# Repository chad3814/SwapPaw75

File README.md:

# SwapPaw75

The SwapPaw75 is a clone of the [Southpaw75](https://github.com/kelvinhall05/Southpaw75) budget FR4 keyboard with support for hotswap sockets.

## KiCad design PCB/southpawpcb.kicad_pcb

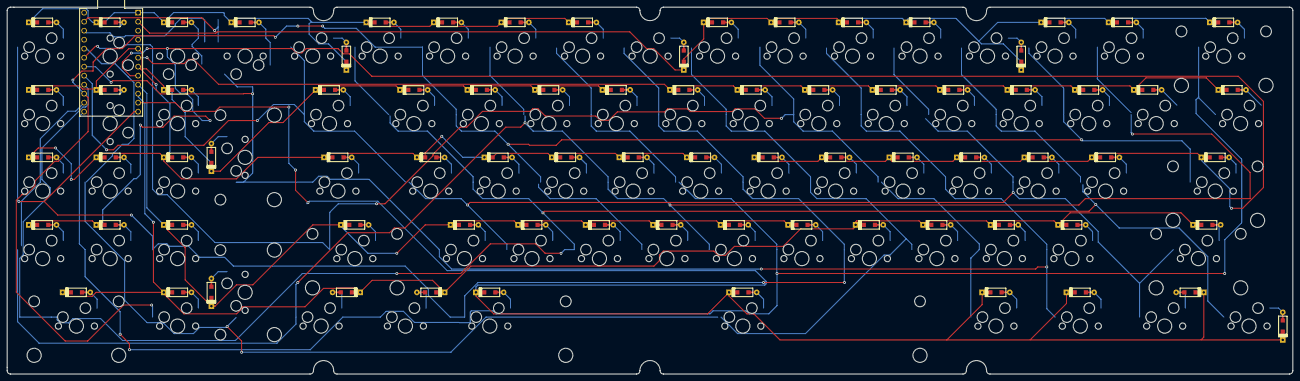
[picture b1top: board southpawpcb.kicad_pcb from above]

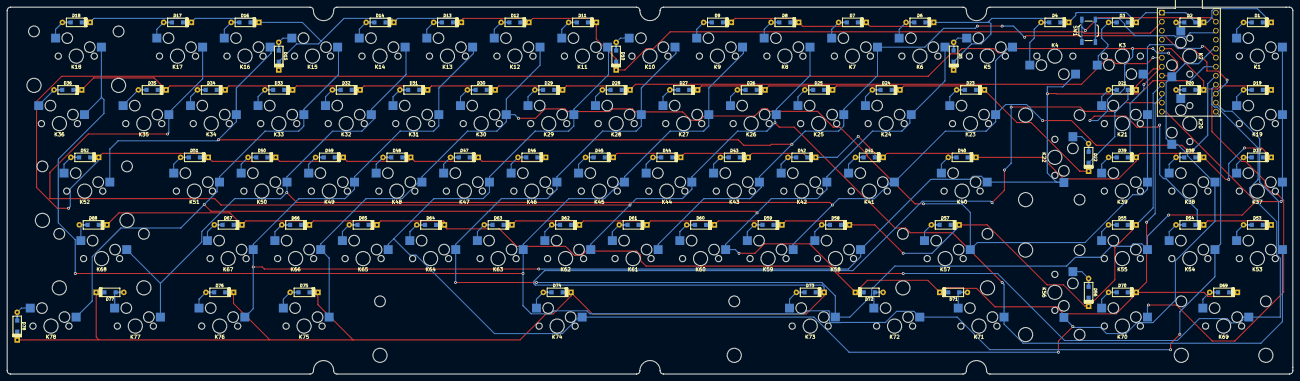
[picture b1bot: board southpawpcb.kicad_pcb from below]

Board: 2 copper layers, 362.9 x 103.6 mm, 158 parts (80 on the bottom side), 98 nets.

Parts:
D1, D2, D3, D4, D5, D6, D7, D8, D9, D10, D11, D12, D13, D14, D15, D16, D17, D18, D19, D20, D21, D22, D23, D24, D25, D26, D27, D28, D29, D30, D31, D32, D33, D34, D35, D36, D37, D38, D39, D40, D41, D42, D43, D44, D45, D46, D47, D48, D49, D50, D51, D52, D53, D54, D55, D56, D57, D58, D59, D60, D61, D62, D63, D64, D65, D66, D67, D68, D69, D70, D71, D72, D73, D74, D75, D76, D77, D78: D; D_SOD123_axial-dual
K1, K2, K3, K4, K5, K6, K7, K8, K9, K10, K11, K12, K13, K14, K15, K16, K17, K19, K20, K21, K24, K25, K26, K27, K28, K29, K30, K31, K32, K33, K34, K35, K37, K38, K39, K41, K42, K43, K44, K45, K46, K47, K48, K49, K50, K51, K53, K54, K55, K58, K59, K60, K61, K62, K63, K64, K65, K66, K67, K70: KEYSW; MXOnly-1U-Hotswap
K18, K22, K56, K69: KEYSW; MXOnly-2U-Hotswap
K23, K36: KEYSW; MXOnly-1.5U-Hotswap
K40: KEYSW; MXOnly-1.75U-Hotswap
K52, K57: KEYSW; MXOnly-2.25U-Hotswap
K68: KEYSW; MXOnly-2.75U-Hotswap
K71, K72, K73, K75, K76, K77, K78: KEYSW; MXOnly-1.25U-Hotswap
K74: KEYSW; MXOnly-6.25U-Hotswap
SW1: Reset; SW_SPST_TL3342
U1: ProMicro

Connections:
unnamed: D1.1 (K), D2.1 (K), D3.1 (K), D4.1 (K), D5.1 (K), D6.1 (K), D7.1 (K), D8.1 (K), D9.1 (K), U1.1 (TX)
unnamed: D1.2 (A), K1.2 (ROW)
unnamed: D2.2 (A), K2.1 (COL)
unnamed: D3.2 (A), K3.1 (COL)
unnamed: D4.2 (A), K4.1 (COL)
unnamed: D5.2 (A), K5.2 (ROW)
unnamed: D6.2 (A), K6.2 (ROW)
unnamed: D7.2 (A), K7.2 (ROW)
unnamed: D8.2 (A), K8.2 (ROW)
unnamed: D9.2 (A), K9.2 (ROW)
unnamed: D10.1 (K), D11.1 (K), D12.1 (K), D13.1 (K), D14.1 (K), D15.1 (K), D16.1 (K), D17.1 (K), D18.1 (K), U1.2 (RX)
unnamed: D10.2 (A), K10.2 (ROW)
unnamed: D11.2 (A), K11.2 (ROW)
unnamed: D12.2 (A), K12.2 (ROW)
unnamed: D13.2 (A), K13.2 (ROW)
unnamed: D14.2 (A), K14.2 (ROW)
unnamed: D15.2 (A), K15.2 (ROW)
unnamed: D16.2 (A), K16.2 (ROW)
unnamed: D17.2 (A), K17.2 (ROW)
unnamed: D18.2 (A), K18.2 (ROW)
unnamed: D19.1 (K), D20.1 (K), D21.1 (K), D22.1 (K), D23.1 (K), D24.1 (K), D25.1 (K), D26.1 (K), D27.1 (K), U1.5 (SCL)
unnamed: D19.2 (A), K19.2 (ROW)
unnamed: D20.2 (A), K20.1 (COL)
unnamed: D21.2 (A), K21.2 (ROW)
unnamed: D22.2 (A), K22.2 (ROW)
unnamed: D23.2 (A), K23.2 (ROW)
unnamed: D24.2 (A), K24.2 (ROW)
unnamed: D25.2 (A), K25.2 (ROW)
unnamed: D26.2 (A), K26.2 (ROW)
unnamed: D27.2 (A), K27.2 (ROW)
unnamed: D28.1 (K), D29.1 (K), D30.1 (K), D31.1 (K), D32.1 (K), D33.1 (K), D34.1 (K), D35.1 (K), D36.1 (K), U1.6 (SDA)
unnamed: D28.2 (A), K28.2 (ROW)
unnamed: D29.2 (A), K29.2 (ROW)
unnamed: D30.2 (A), K30.2 (ROW)
unnamed: D31.2 (A), K31.2 (ROW)
unnamed: D32.2 (A), K32.2 (ROW)
unnamed: D33.2 (A), K33.2 (ROW)
unnamed: D34.2 (A), K34.2 (ROW)
unnamed: D35.2 (A), K35.2 (ROW)
unnamed: D36.2 (A), K36.2 (ROW)
unnamed: D37.1 (K), D38.1 (K), D39.1 (K), D40.1 (K), D41.1 (K), D42.1 (K), D43.1 (K), D44.1 (K), D45.1 (K), U1.7 (D4)
unnamed: D37.2 (A), K37.2 (ROW)
unnamed: D38.2 (A), K38.2 (ROW)
unnamed: D39.2 (A), K39.2 (ROW)
unnamed: D40.2 (A), K40.2 (ROW)
unnamed: D41.2 (A), K41.2 (ROW)
unnamed: D42.2 (A), K42.2 (ROW)
unnamed: D43.2 (A), K43.2 (ROW)
unnamed: D44.2 (A), K44.2 (ROW)
unnamed: D45.2 (A), K45.2 (ROW)
unnamed: D46.1 (K), D47.1 (K), D48.1 (K), D49.1 (K), D50.1 (K), D51.1 (K), D52.1 (K), D53.1 (K), D54.1 (K), U1.8 (C6)
unnamed: D46.2 (A), K46.2 (ROW)
unnamed: D47.2 (A), K47.2 (ROW)
unnamed: D48.2 (A), K48.2 (ROW)
unnamed: D49.2 (A), K49.2 (ROW)
unnamed: D50.2 (A), K50.2 (ROW)
unnamed: D51.2 (A), K51.2 (ROW)
unnamed: D52.2 (A), K52.2 (ROW)
unnamed: D53.2 (A), K53.2 (ROW)
unnamed: D54.2 (A), K54.2 (ROW)
unnamed: D55.1 (K), D56.1 (K), D57.1 (K), D58.1 (K), D59.1 (K), D60.1 (K), D61.1 (K), D62.1 (K), D63.1 (K), U1.9 (D7)
unnamed: D55.2 (A), K55.2 (ROW)
unnamed: D56.2 (A), K56.2 (ROW)
unnamed: D57.2 (A), K57.2 (ROW)
unnamed: D58.2 (A), K58.2 (ROW)
unnamed: D59.2 (A), K59.2 (ROW)
unnamed: D60.2 (A), K60.2 (ROW)
unnamed: D61.2 (A), K61.2 (ROW)
unnamed: D62.2 (A), K62.2 (ROW)
unnamed: D63.2 (A), K63.2 (ROW)
unnamed: D64.1 (K), D65.1 (K), D66.1 (K), D67.1 (K), D68.1 (K), D69.1 (K), D70.1 (K), D71.1 (K), D72.1 (K), U1.10 (E6)
unnamed: D64.2 (A), K64.2 (ROW)
unnamed: D65.2 (A), K65.2 (ROW)
unnamed: D66.2 (A), K66.2 (ROW)
unnamed: D67.2 (A), K67.2 (ROW)
unnamed: D68.2 (A), K68.2 (ROW)
unnamed: D69.2 (A), K69.2 (ROW)
unnamed: D70.2 (A), K70.2 (ROW)
unnamed: D71.2 (A), K71.2 (ROW)
unnamed: D72.2 (A), K72.2 (ROW)
unnamed: D73.1 (K), D74.1 (K), D75.1 (K), D76.1 (K), D77.1 (K), D78.1 (K), U1.11 (B4)
unnamed: D73.2 (A), K73.2 (ROW)
unnamed: D74.2 (A), K74.2 (ROW)
unnamed: D75.2 (A), K75.2 (ROW)
unnamed: D76.2 (A), K76.2 (ROW)
unnamed: D77.2 (A), K77.2 (ROW)
unnamed: D78.2 (A), K78.2 (ROW)
unnamed: K1.1 (COL), K10.1 (COL), K19.1 (COL), K28.1 (COL), K37.1 (COL), K46.1 (COL), K55.1 (COL), K64.1 (COL), K73.1 (COL), U1.12 (B5)
unnamed: K2.2 (ROW), K11.1 (COL), K20.2 (ROW), K29.1 (COL), K38.1 (COL), K47.1 (COL), K56.1 (COL), K65.1 (COL), K74.1 (COL), U1.20 (F4)
unnamed: K3.2 (ROW), K12.1 (COL), K21.1 (COL), K30.1 (COL), K39.1 (COL), K48.1 (COL), K57.1 (COL), K66.1 (COL), K75.1 (COL), U1.19 (F5)
unnamed: K4.2 (ROW), K13.1 (COL), K22.1 (COL), K31.1 (COL), K40.1 (COL), K49.1 (COL), K58.1 (COL), K67.1 (COL), K76.1 (COL), U1.18 (F6)
unnamed: K5.1 (COL), K14.1 (COL), K23.1 (COL), K32.1 (COL), K41.1 (COL), K50.1 (COL), K59.1 (COL), K68.1 (COL), K77.1 (COL), U1.17 (F7)
unnamed: K6.1 (COL), K15.1 (COL), K24.1 (COL), K33.1 (COL), K42.1 (COL), K51.1 (COL), K60.1 (COL), K69.1 (COL), K78.1 (COL), U1.16 (B1)
unnamed: K7.1 (COL), K16.1 (COL), K25.1 (COL), K34.1 (COL), K43.1 (COL), K52.1 (COL), K61.1 (COL), K70.1 (COL), U1.15 (B3)
unnamed: K8.1 (COL), K17.1 (COL), K26.1 (COL), K35.1 (COL), K44.1 (COL), K53.1 (COL), K62.1 (COL), K71.1 (COL), U1.14 (B2)
unnamed: K9.1 (COL), K18.1 (COL), K27.1 (COL), K36.1 (COL), K45.1 (COL), K54.1 (COL), K63.1 (COL), K72.1 (COL), U1.13 (B6)
unnamed: SW1.1, U1.23 (GND)
unnamed: SW1.2, U1.22 (RST)

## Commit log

2021-04-13 add submodules
2021-04-13 attempt at retracing
2021-04-25 all routed
2021-04-25 move zip file
2021-04-25 final
2021-04-25 remove README
2021-04-25 updated readme
    fix my bad markdown
